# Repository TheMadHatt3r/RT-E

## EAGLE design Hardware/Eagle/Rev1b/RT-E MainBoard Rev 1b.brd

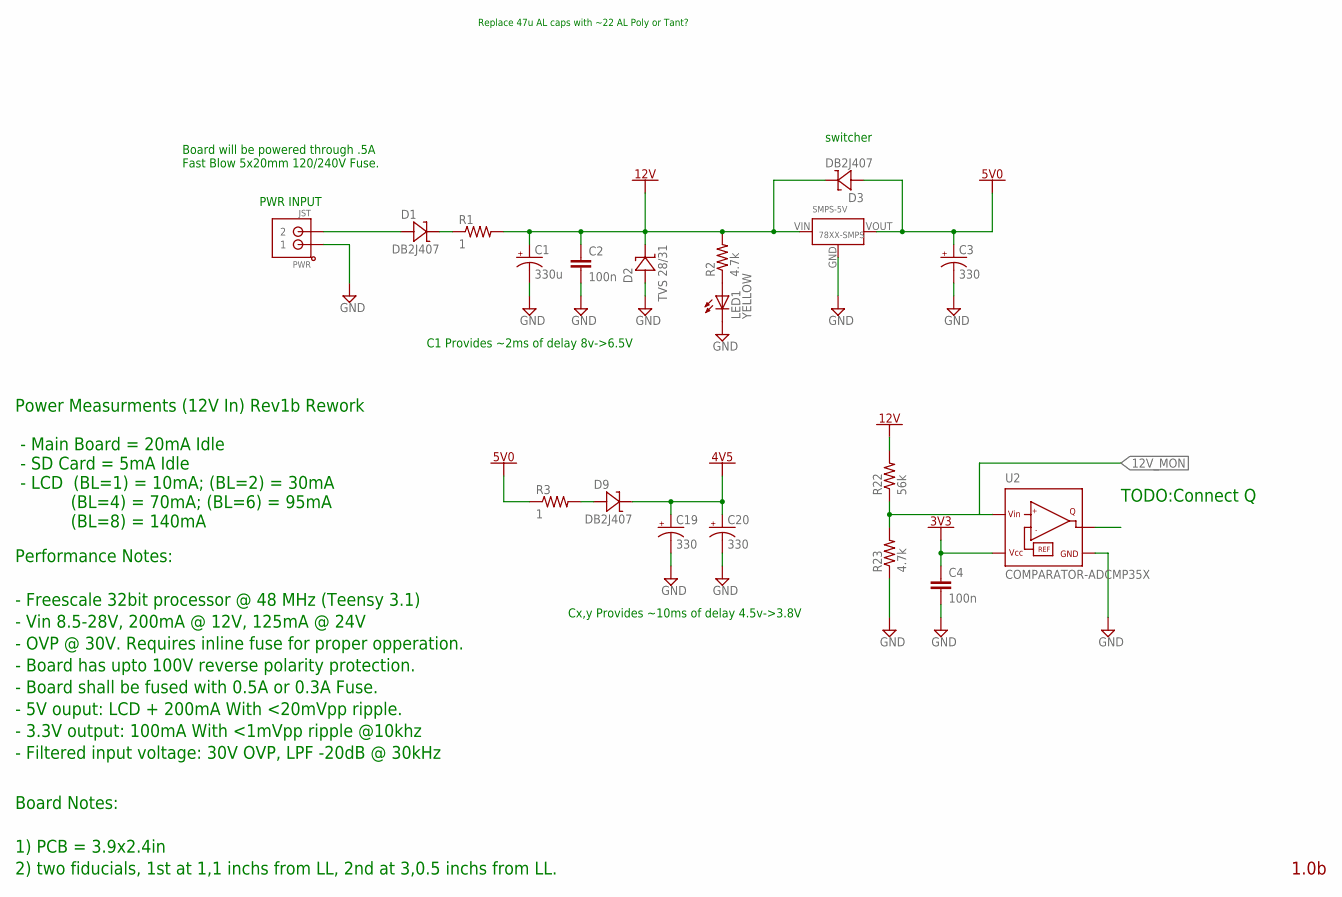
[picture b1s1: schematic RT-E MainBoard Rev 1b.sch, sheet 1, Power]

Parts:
C1: 330u; E5-10,5
C2, C4: 100n; C0603K
C3, C19, C20: 330; E2,5-7
D1, D3, D9: DB2J407; SOD323R_INFINEON
D2: TVS 28/31; DO-214AC(SMA)
LED1: YELLOW; CHIP-LED0603
PWR: JST; JST_B2B-PH_HEADER
R1, R3: 1; R1206
R2, R23: 4.7k; R0603
R22: 56k; R0603
SMPS-5V: 78XX-SMPS
U2: COMPARATOR-ADCMP35X; SC70-4L

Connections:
3V3: C4.1, C19.+, C20.+, D9.C, U2.5 (VCC); also elsewhere on the board
5V0: C3.+, D3.A, R3.1, SMPS-5V.VOUT; also elsewhere on the board
12V: C1.+, C2.1, D2.P$1, D3.C, R1.2, R2.2, R22.2, SMPS-5V.VIN; also elsewhere on the board
GND: C1.-, C2.2, C3.-, C4.2, C19.-, C20.-, D2.P$2, LED1.C, PWR.P1 (1), R23.1, SMPS-5V.GND, U2.3 (GND); also elsewhere on the board
unnamed: D1.C, R1.1
unnamed: LED1.A, R2.1
unnamed: R22.1, R23.2, U2.1 (VIN)
unnamed: D9.A, R3.2
unnamed: D1.A, PWR.P2 (2)

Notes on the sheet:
Board will be powered through .5A Fast Blow 5x20mm 120/240V Fuse.
switcher
Board Notes: 1) PCB = 3.9x2.4in 2) two fiducials, 1st at 1,1 inchs from LL, 2nd at 3,0.5 inchs from LL.
PWR INPUT
1.0b
Performance Notes: - Freescale 32bit processor @ 48 MHz (Teensy 3.1) - Vin 8.5-28V, 200mA @ 12V, 125mA @ 24V - OVP @ 30V. Requires inline fuse for proper opperation. - Board has upto 100V reverse polarity protection. - Board shall be fused with 0.5A or 0.3A Fuse. - 5V ouput: LCD + 200mA With <20mVp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
Power Measurments (12V In) Rev1b Rework - Main Board = 20mA Idle - SD Card = 5mA Idle - LCD (BL=1) = 10mA; (BL=2) = 30mA (BL=4) = 70mA; (BL=6) = 95mA (BL=8) = 140mA
Replace 47u AL caps with ~22 AL Poly or Tant?
C1 Provides ~2ms of delay 8v->6.5V
TODO:Connect Q
Cx,y Provides ~10ms of delay 4.5v->3.8V

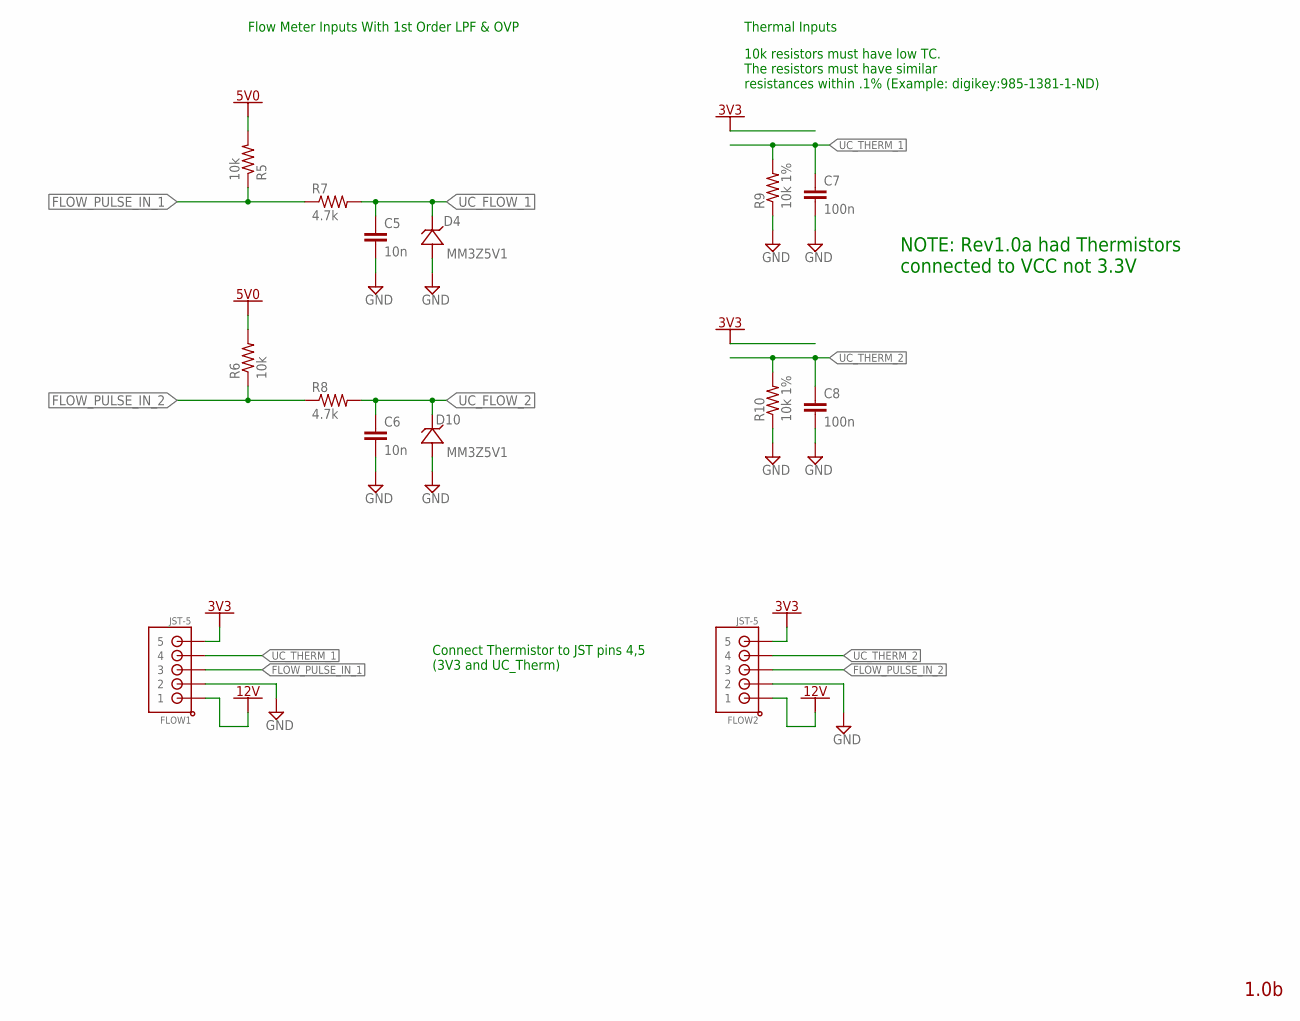
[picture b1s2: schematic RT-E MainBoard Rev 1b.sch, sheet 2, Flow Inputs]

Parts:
C5, C6: 10n; C0603K
C7, C8: 100n; C0603K
D4, D10: MM3Z5V1; SOD323R_INFINEON
FLOW1, FLOW2: JST-5; JST_B5B-PH_HEADER
R5, R6: 10k; R0603
R7, R8: 4.7k; R0603
R9, R10: 10k 1%; R0603

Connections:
3V3: FLOW1.P5 (5), FLOW2.P5 (5); also elsewhere on the board
5V0: R5.2, R6.2; also elsewhere on the board
12V: FLOW1.P1 (1), FLOW2.P1 (1); also elsewhere on the board
FLOW_PULSE_IN_1: FLOW1.P3 (3), R5.1, R7.1
FLOW_PULSE_IN_2: FLOW2.P3 (3), R6.1, R8.1
GND: C5.2, C6.2, C7.2, C8.2, D4.A, D10.A, FLOW1.P2 (2), FLOW2.P2 (2), R9.1, R10.1; also elsewhere on the board
UC_FLOW_1: C5.1, D4.C, R7.2; also elsewhere on the board
UC_FLOW_2: C6.1, D10.C, R8.2; also elsewhere on the board
UC_THERM_1: C7.1, FLOW1.P4 (4), R9.2; also elsewhere on the board
UC_THERM_2: C8.1, FLOW2.P4 (4), R10.2; also elsewhere on the board

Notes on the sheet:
Flow Meter Inputs With 1st Order LPF & OVP
Thermal Inputs
10k resistors must have low TC. The resistors must have similar resistances within .1% (Example: digikey:985-1381-1-ND)
1.0b
NOTE: Rev1.0a had Thermistors connected to VCC not 3.3V
Connect Thermistor to JST pins 4,5 (3V3 and UC_Therm)

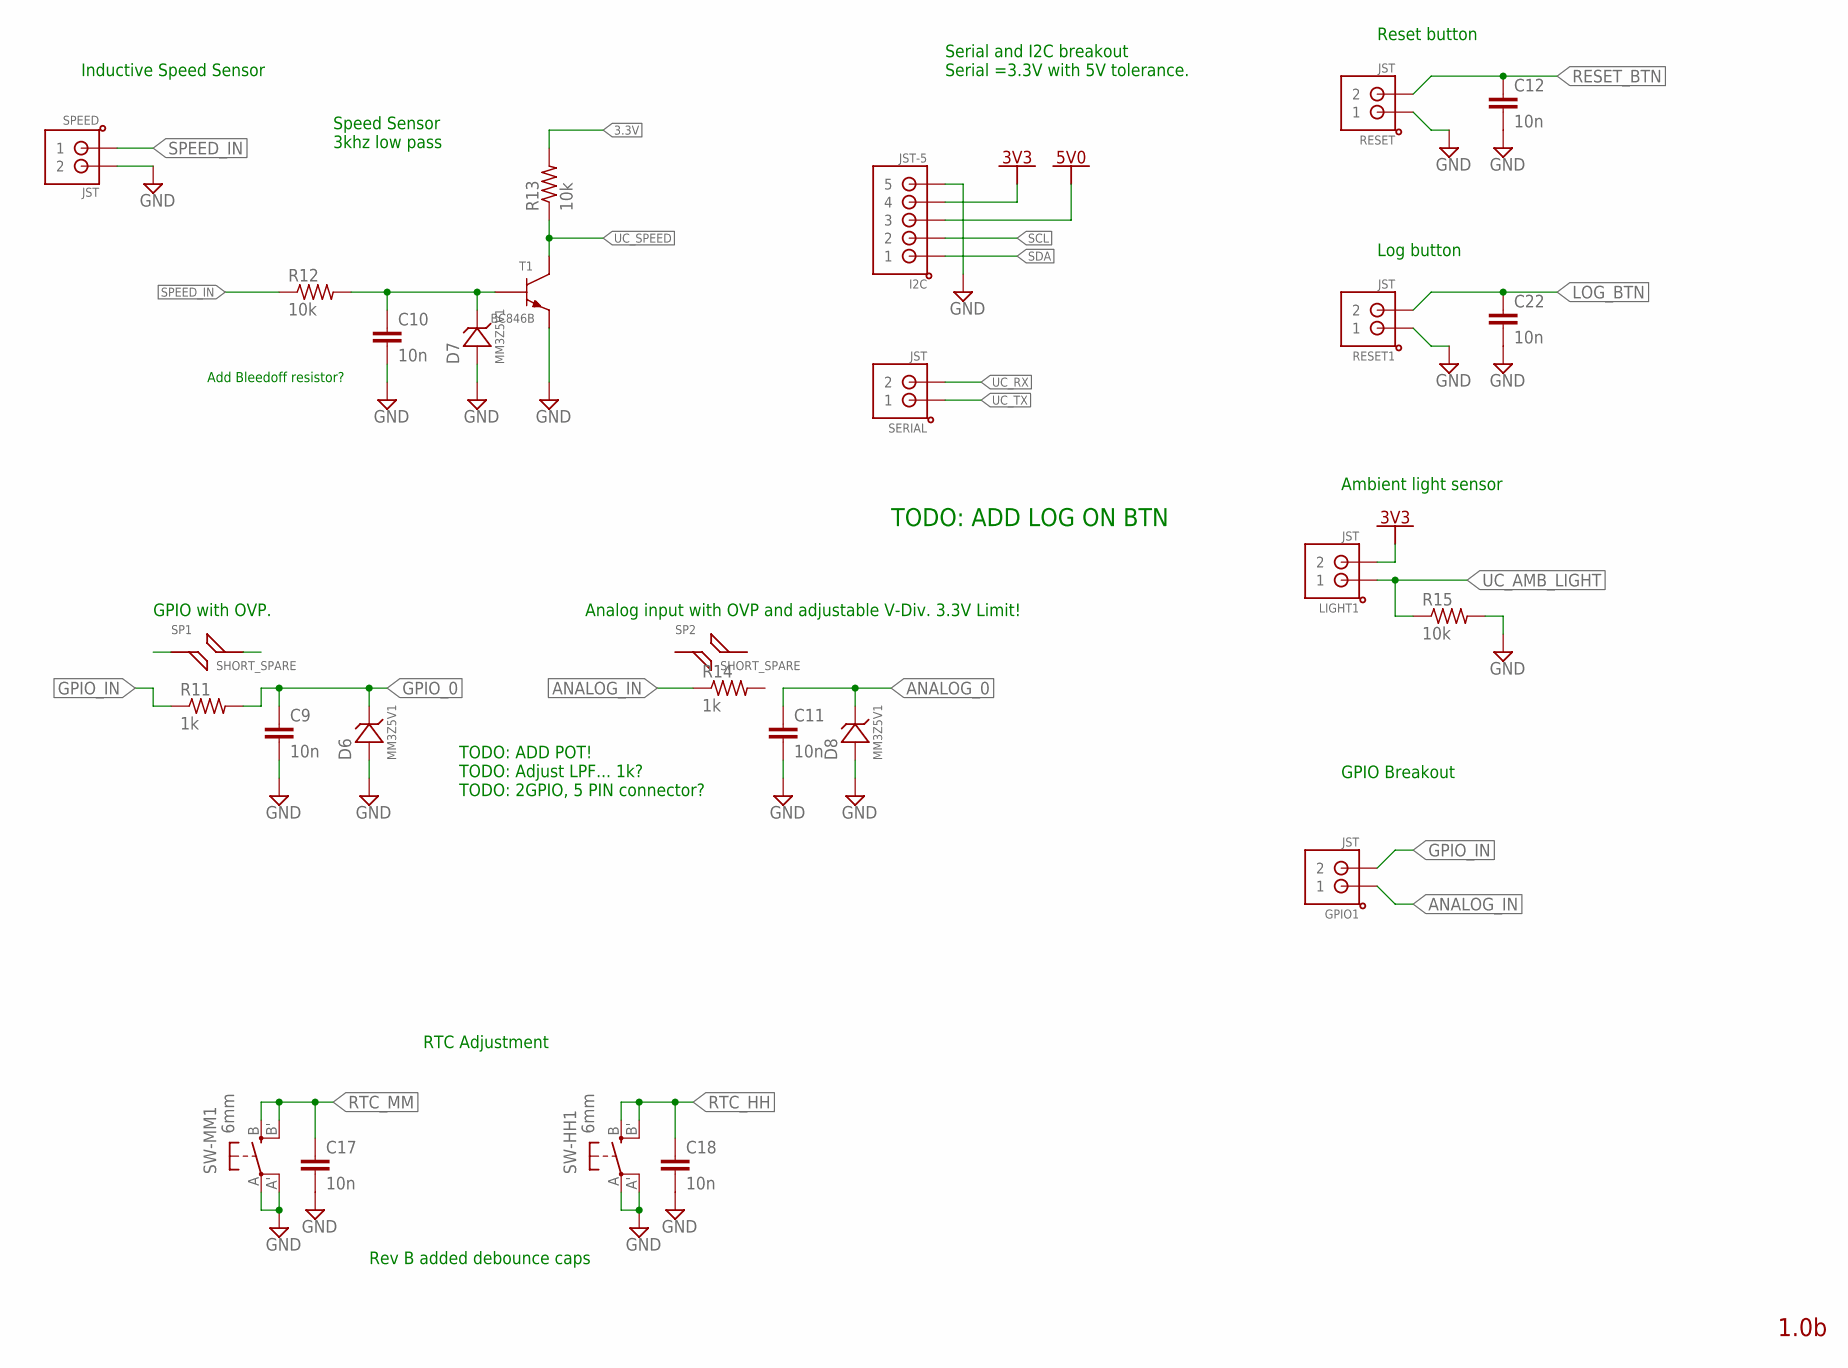
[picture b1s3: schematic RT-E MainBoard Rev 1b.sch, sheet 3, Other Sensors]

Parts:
C9, C10, C11, C12, C17, C18, C22: 10n; C0603K
D6, D7, D8: MM3Z5V1; SOD323-W
GPIO1: JST; JST_B2B-PH_HEADER
I2C: JST-5; JST_B5B-PH_HEADER
LIGHT1: JST; JST_B2B-PH_HEADER
R11, R14: 1k; R0603
R12, R13, R15: 10k; R0603
RESET, RESET1: JST; JST_B2B-PH_HEADER
SERIAL: JST; JST_B2B-PH_HEADER
SP1, SP2: SHORT_SPARE; SHORT_0603
SPEED: JST; JST_B2B-PH_HEADER
SW-HH1: 6mm; EVQ-Q2
SW-MM1: 6mm; EVQ-Q2
T1: BC846B; BJT-BC846

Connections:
3.3V: R13.2; also elsewhere on the board
3V3: I2C.P4 (4), LIGHT1.P2 (2); also elsewhere on the board
5V0: I2C.P3 (3); also elsewhere on the board
ANALOG_0: C11.1, D8.C; also elsewhere on the board
ANALOG_IN: GPIO1.P1 (1), R14.1
GND: C9.2, C10.2, C11.2, C12.2, C17.2, C18.2, C22.2, D6.A, D7.A, D8.A, I2C.P5 (5), R15.2, RESET.P1 (1), RESET1.P1 (1), SPEED.P2 (2), SW-HH1.A, SW-HH1.A' (P1), SW-MM1.A, SW-MM1.A' (P1), T1.E; also elsewhere on the board
GPIO_0: C9.1, D6.C, R11.2; also elsewhere on the board
GPIO_IN: GPIO1.P2 (2), R11.1
LOG_BTN: C22.1, RESET1.P2 (2); also elsewhere on the board
unnamed: C10.1, D7.C, R12.2, T1.B
RESET_BTN: C12.1, RESET.P2 (2); also elsewhere on the board
RTC_HH: C18.1, SW-HH1.B (S), SW-HH1.B' (S1); also elsewhere on the board
RTC_MM: C17.1, SW-MM1.B (S), SW-MM1.B' (S1); also elsewhere on the board
SCL: I2C.P2 (2); also elsewhere on the board
SDA: I2C.P1 (1); also elsewhere on the board
SPEED_IN: R12.1, SPEED.P1 (1)
UC_AMB_LIGHT: LIGHT1.P1 (1), R15.1; also elsewhere on the board
UC_RX: SERIAL.P2 (2); also elsewhere on the board
UC_SPEED: R13.1, T1.C; also elsewhere on the board
UC_TX: SERIAL.P1 (1); also elsewhere on the board

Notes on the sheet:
Speed Sensor 3khz low pass
Reset button
RTC Adjustment
GPIO with OVP.
Analog input with OVP and adjustable V-Div. 3.3V Limit!
TODO: ADD POT! TODO: Adjust LPF... 1k? TODO: 2GPIO, 5 PIN connector?
Serial and I2C breakout Serial =3.3V with 5V tolerance.
GPIO Breakout
Ambient light sensor
Inductive Speed Sensor
1.0b
Rev B added debounce caps
Add Bleedoff resistor?
TODO: ADD LOG ON BTN
Log button

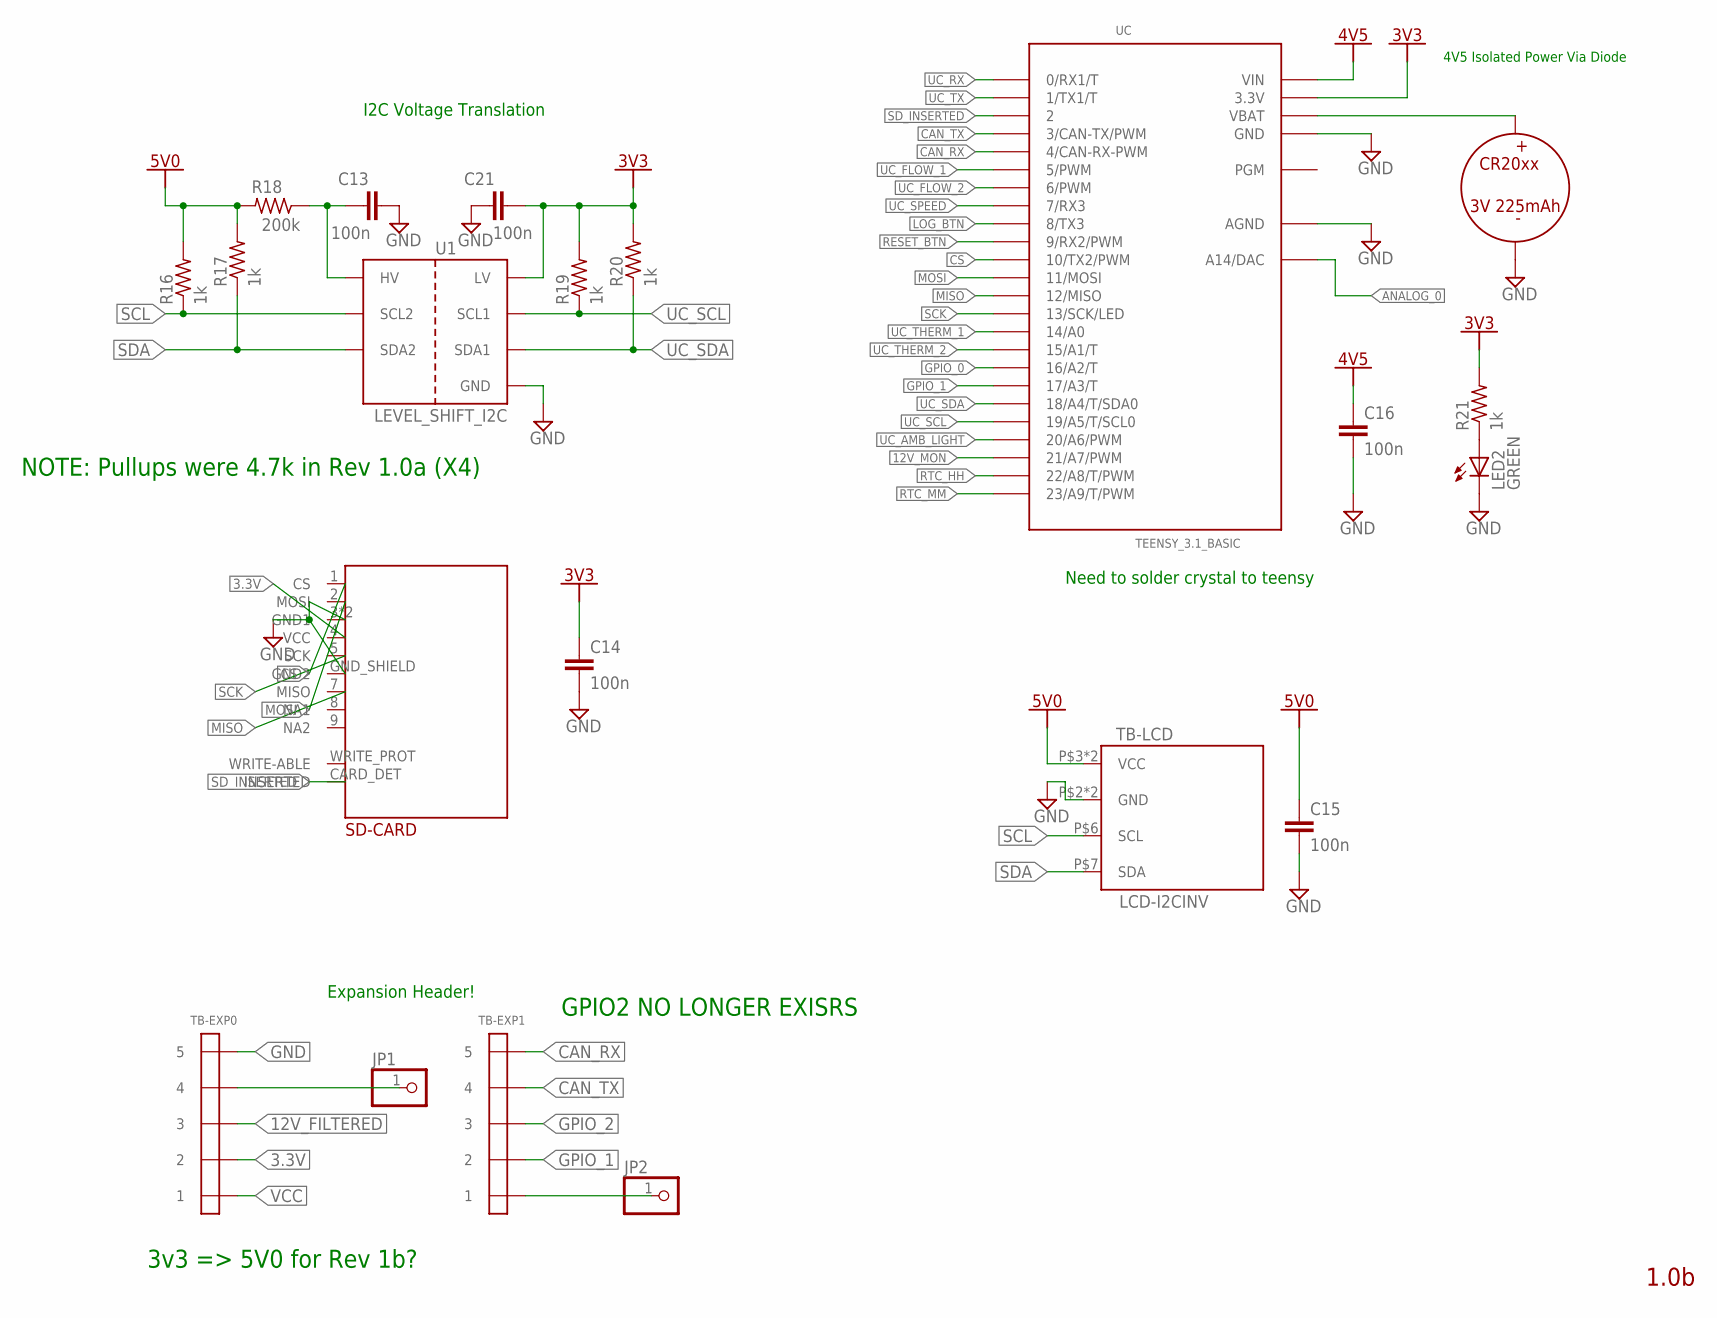
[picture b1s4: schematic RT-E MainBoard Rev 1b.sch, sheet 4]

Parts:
BAT: 3V_LITH_20MM; COIN_CELL_HORZ_20MM
C13, C14, C15, C16, C21: 100n; C0603K
JP1, JP2: PINHD-1X1CB; 1X01-CLEANBIG
LED2: GREEN; CHIP-LED0603
R16, R17, R19, R20, R21: 1k; R0603
R18: 200k; R0603
SD-CARD: A101492CT-ND; SD-CARD-1
TB-EXP0, TB-EXP1: EXPANSION_HEADER_5; HEADER_1X5_2.54MM
TB-LCD: LCD-I2CINV; LCD_I2C_INV
U1: LEVEL_SHIFT_I2C; SO08
UC: TEENSY_3.1_BASIC

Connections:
3.3V: SD-CARD.4 (VCC), TB-EXP0.P$2 (2); also elsewhere on the board
3V3: C14.1, C21.2, R19.2, R20.2, R21.2, U1.2 (LV), UC.3.3V, UC.3.3V1 (3.3V); also elsewhere on the board
4V5: C16.1, UC.VIN
5V0: C15.1, R16.2, R17.2, R18.2, TB-LCD.P$3 (VCC), TB-LCD.P$9 (VCC); also elsewhere on the board
12V_FILTERED: TB-EXP0.P$3 (3)
12V_MON: UC.21/A7 (21/A7/PWM)
ANALOG_0: UC.A14 (A14/DAC); also elsewhere on the board
CAN_RX: TB-EXP1.P$5 (5), UC.4 (4/CAN-RX-PWM)
CAN_TX: TB-EXP1.P$4 (4), UC.3 (3/CAN-TX/PWM)
CS: SD-CARD.1 (CS), UC.10 (10/TX2/PWM)
GND: BAT.NEG (-), C13.2, C14.2, C15.2, C16.2, C21.1, LED2.C, SD-CARD.3 (GND1), SD-CARD.6 (GND1), SD-CARD.GND_SHIELD (GND2), TB-EXP0.P$5 (5), TB-LCD.P$2 (GND), TB-LCD.P$8 (GND), U1.1 (GND), UC.AGND, UC.GND, UC.GND1 (GND); also elsewhere on the board
GPIO_0: UC.16/A2 (16/A2/T); also elsewhere on the board
GPIO_1: TB-EXP1.P$2 (2), UC.17/A3 (17/A3/T)
GPIO_2: TB-EXP1.P$3 (3)
LOG_BTN: UC.8 (8/TX3); also elsewhere on the board
MISO: SD-CARD.7 (MISO), UC.12 (12/MISO)
MOSI: SD-CARD.2 (MOSI), UC.11 (11/MOSI)
unnamed: LED2.A, R21.1
unnamed: JP1.1, TB-EXP0.P$4 (4)
unnamed: C13.1, R18.1, U1.7 (HV), U1.8 (HV)
unnamed: BAT.POS (+), UC.VBAT
unnamed: JP2.1, TB-EXP1.P$1 (1)
RESET_BTN: UC.9 (9/RX2/PWM); also elsewhere on the board
RTC_HH: UC.22/A8 (22/A8/T/PWM); also elsewhere on the board
RTC_MM: UC.23/A9 (23/A9/T/PWM); also elsewhere on the board
SCK: SD-CARD.5 (SCK), UC.13 (13/SCK/LED)
SCL: R16.1, TB-LCD.P$6 (SCL), U1.6 (SCL2); also elsewhere on the board
SDA: R17.1, TB-LCD.P$7 (SDA), U1.5 (SDA2); also elsewhere on the board
SD_INSERTED: SD-CARD.CARD_DET (INSERTED), UC.2
UC_AMB_LIGHT: UC.20/A6 (20/A6/PWM); also elsewhere on the board
UC_FLOW_1: UC.5 (5/PWM); also elsewhere on the board
UC_FLOW_2: UC.6 (6/PWM); also elsewhere on the board
UC_RX: UC.0 (0/RX1/T); also elsewhere on the board
UC_SCL: R19.1, U1.3 (SCL1), UC.19/A5 (19/A5/T/SCL0)
UC_SDA: R20.1, U1.4 (SDA1), UC.18/A4 (18/A4/T/SDA0)
UC_SPEED: UC.7 (7/RX3); also elsewhere on the board
UC_THERM_1: UC.14/A0; also elsewhere on the board
UC_THERM_2: UC.15/A1 (15/A1/T); also elsewhere on the board
UC_TX: UC.1 (1/TX1/T); also elsewhere on the board
VCC: TB-EXP0.P$1 (1)

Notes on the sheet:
I2C Voltage Translation
Need to solder crystal to teensy
Expansion Header!
1.0b
NOTE: Pullups were 4.7k in Rev 1.0a (X4)
3v3 => 5V0 for Rev 1b?
4V5 Isolated Power Via Diode
GPIO2 NO LONGER EXISRS

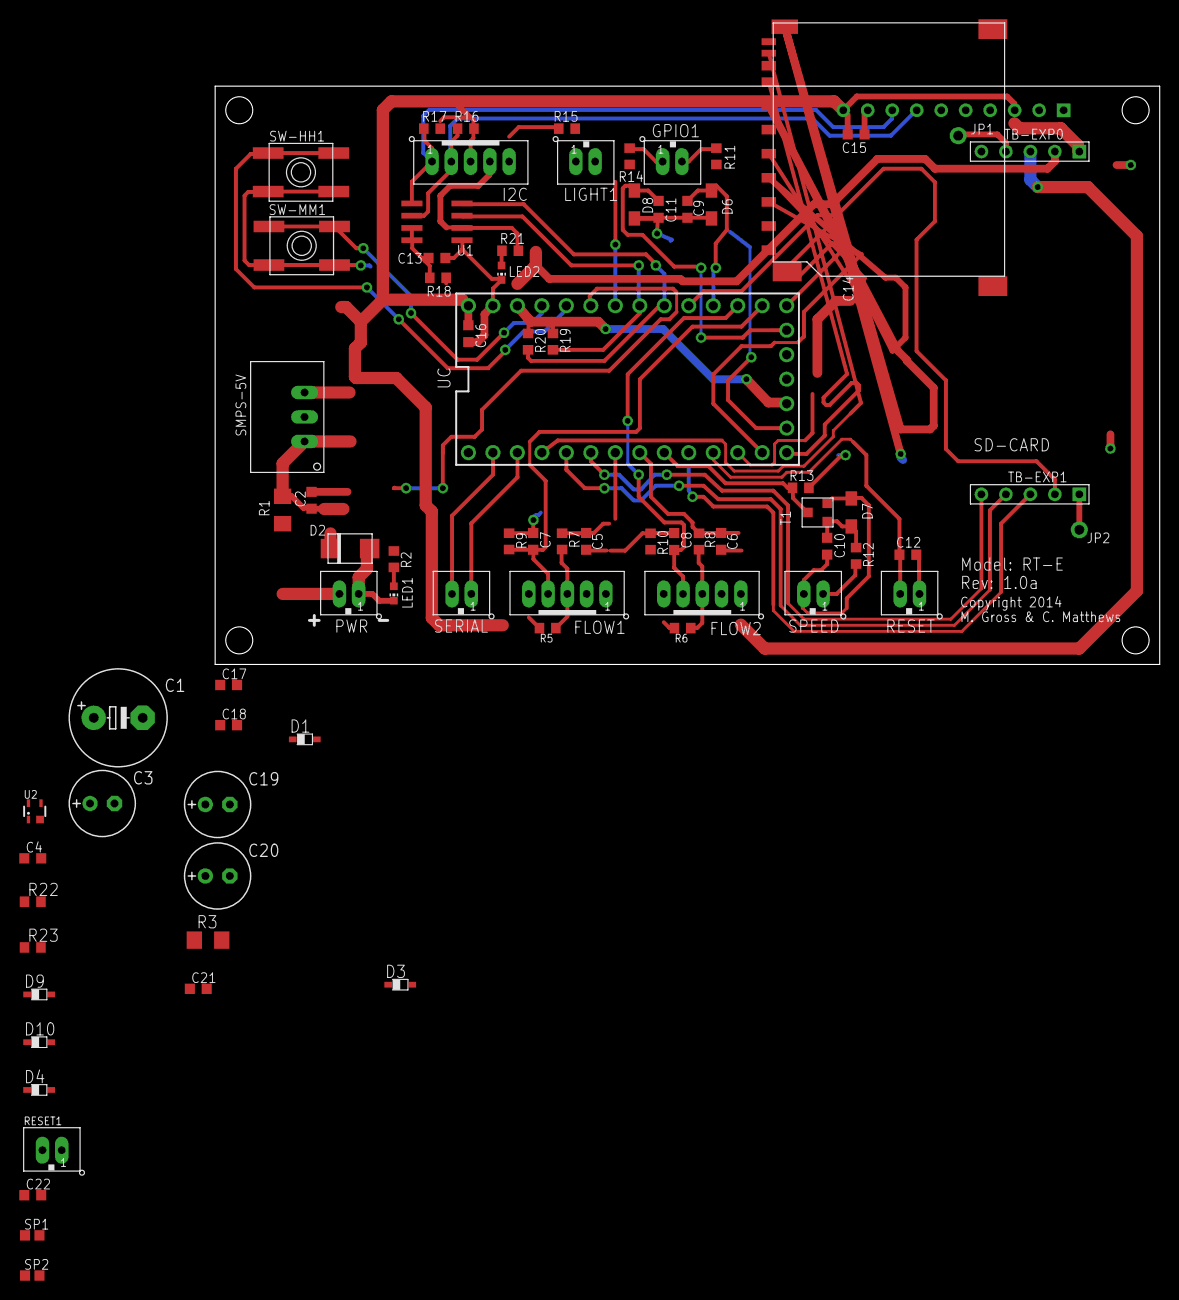
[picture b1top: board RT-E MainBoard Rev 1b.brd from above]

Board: 2 copper layers, 98.0 x 60.0 mm, 81 parts (1 on the bottom side), 48 nets.

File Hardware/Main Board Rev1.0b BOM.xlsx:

PART on Schematic | Description | Digikey P/N | Qty | Cost / per | Cost 10x |  | Sub Total | Package | Pads | Pad Sum
R2,R4, R7, R8, R11, R14 | RES 4.7k 1% | RHM4.70KCFCT-ND | 6 | 0.01 |  | x10 | 0.06 | 603 | 2 | 12
R5, R6, R12, R13, R15 | RES 10k 1% | RHM10.0KCFCT-ND | 5 | 1.0999999999999999E-2 |  | x10 | 5.4999999999999993E-2 | 603 | 2 | 10
R9, R10 | RES 10k .1% TC=10ppm | 985-1381-1-ND | 2 | 0.76 |  | x1 | 1.52 | 603 | 2 | 4 |  | 8.3000000000000007
 | RES 56k 1% | RMCF0603FT56K0CT-ND | 1 | 2.5000000000000001E-2 | 0.1 | x10 | 2.5000000000000001E-2 | 603 | 2 | 2 |  | 4.7 | 0.62384375445318807 | 0.60115343305885471
R16, R17, R19, R20, R21 | RES 1k 1% |  | 5 |  |  |  |  |  |  |  |  | 59
R1 | RES 1.0 1% | 311-1.00FRCT-ND | 1 | 3.2000000000000001E-2 |  | x10 | 3.2000000000000001E-2 | 1206 | 2 | 2
R18 | RES 200k | 311-200KGRCT-ND | 1 | 1.0999999999999999E-2 |  | x10 | 1.0999999999999999E-2 | 603 | 2 | 2
LED2 | LED GREEN | 754-1121-1-ND | 1 | 0.11700000000000001 |  | x10 | 0.11700000000000001 | 603 | 2 | 2
LED1 | LED Yellow | 475-1196-1-ND | 1 | 0.14299999999999999 |  | x10 | 0.14299999999999999 | 603 | 2 | 2 |  |  |  | L | W
C5, C6, C9, C10, C11, C12 | CAP 10nF 50V 10% | 1276-1009-1-ND | 6 | 1.7999999999999999E-2 |  | x10 | 0.10799999999999998 | 603 | 2 | 12 |  |  | SOD-323 | 2.5 | 1.3 | 9.8425196850393706E-2 | 5.1181102362204731E-2
C2, C7, C8, C13, C14, C15, C16 | CAP 100nF 50V 10% | 1276-1936-1-ND | 7 | 0.02 |  | x10 | 0.14000000000000001 | 603 | 2 | 14 |  |  | SOD-123 | 3.8 | 1.8 | 0.14960629921259844 | 7.0866141732283464E-2
 | CAP 330uF 50V | 493-1343-ND |  | 0.48 | 0.34 | x10 | 0 | TH-5MM | 0 | 0 |  |  | SMA | 5.2 | 2.6 | 0.20472440944881892 | 0.10236220472440946
 | CAP 330uF 10V | 1189-2177-ND |  | 0.35 | 0.24 |  | 0 | TH-2.5MM
T1 | BJT (BC846B) 200x 30V | 568-1632-6-ND | 1 | 0.14000000000000001 |  |  | 0.14000000000000001 |  | 3 | 3
SMPS-5V | 5V SMPS | 945-1037-ND | 1 | 6.81 |  |  | 6.81 | TH | 0 | 0
 | Schottky 40V 0.5A | DB2J40700LCT-ND |  | 0.41 | 0.3 |  | 0 | SOD-323 | 2 | 0 |  | 4095 | 0.80586080586080588
D2 | TVS 28/31 | SMAJ28CALFCT-ND | 1 | 0.47 |  |  | 0.47 | SMA | 2 | 2 |  | 3300
D4, D5, D7, D6, D8 | 5.1V Zener | MM3Z5V1ST1GOSCT-ND | 5 | 0.13 |  | x10 | 0.65 | SOD-323 | 2 | 10
U1 | 5-> 3.3 V level shifter | 568-4215-1-ND | 1 | 0.78 |  | x1 | 0.78 | SOIC-8 | 8 | 8
SW-MM1, SW-HH1 | PUSHBUTTON - 6MM | CKN9112CT-ND | 2 | 0.2 |  | x10 | 0.4 | 6MM SMD | 4 | 8
UC (2 long sides) | Headers-F-14 | S7047-ND | 2 | 0.98 |  | x10 | 1.96 | TH | 0 | 0
TB-EXP0,TB-EXP1, TB-LCD, UC(short side) | Headers-F-5 | S7038-ND | 5 | 0.5 |  | x10 | 2.5 | TH | 0 | 0
FLOW1, FLOW2, I2C | JST-5 | 455-1707-ND | 3 | 0.26 |  | x10 | 0.78 | TH | 0 | 0
SERIAL, RESET,SPEED,LIGHT1,GPIO1,PWR | JST-2 | 455-1704-ND | 6 | 0.15 |  | x10 | 0.89999999999999991 | TH | 0 | 0
SD | SD Card Slot | A101492CT-ND | 1 | 3.44 |  | 1x | 3.44 | SMD | 9 | 9
 | Comparator | ADCMP356YKSZ-REEL7CT-ND |  | 0.93 | 0.82 |  |  | SMD
BAT | BAT 3V 2032 | P657-ND | 1 | 1.06 |  | 1.06 | 1.06 | SMD | 2 | 2
 |  | Component Count | 65 |  |  |  |  |  | Pads | 104

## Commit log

2017-10-30 Inital Code
2017-10-30 Added Hardware + Manual 9+ Private

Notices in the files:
Hardware/Eagle/Rev1b/RT-E MainBoard Rev 1b.brd:
Copyright 2014
